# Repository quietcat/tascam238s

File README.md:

# The Missing Tascam 238S Service Manual
Tascam 238S schematics and additional information. The Dolby S daughtercards are also used in Tascam MSR

## rp-amp-pcb

https://github.com/quietcat/tascam238s/blob/main/rp-amp-pcb.pdf

Contains Kicad schematics for the part of Tascam 238S channel PCB that is different from the dbx version

## dolby-hic

https://github.com/quietcat/tascam238s/blob/main/dolby-hic.pdf

Contains Kicad schematics for Dolby S NR HIC PCB, a Dolby encoder/decoder daughtercard for Tascam 238S

https://github.com/quietcat/tascam238s/tree/main/dolby-hic/gerbers contains Gerber files for a replacement Dolby PCB. The layout is different from the original, but functionally it is the same.

Visit https://238pro.com for more information on Tascam 238/238S repair and service

## 238S Calibration

First, calibrate the unit with Dolby S out.

Set all channels to recording mode, then press Pause and Record.

Feed -10 dBV/0 dBVU 400Hz (316 mV RMS) signal to the line inputs, and use ENC ADJ trimmer to adjust AC voltage on TP1 to be 388 mV.

Use ENC OUT trimmer to adjust AC voltage on REC LEVEL trimmer input lead (closest to the front) to be the same in both Dolby IN and OUT modes on each channel.

With Dolby S OUT, make a recording of -10 dBV/0 dBVU 400Hz test tone on all channels.

Set Dolby to IN, play back the recording and use DEC ADJ trimmer to adjust AC voltage on TP1 to be 388 mV on all channels.

Use DEC OUT trimmer to set voltage on the line out to -10 dBV (316 mV) on all channels.

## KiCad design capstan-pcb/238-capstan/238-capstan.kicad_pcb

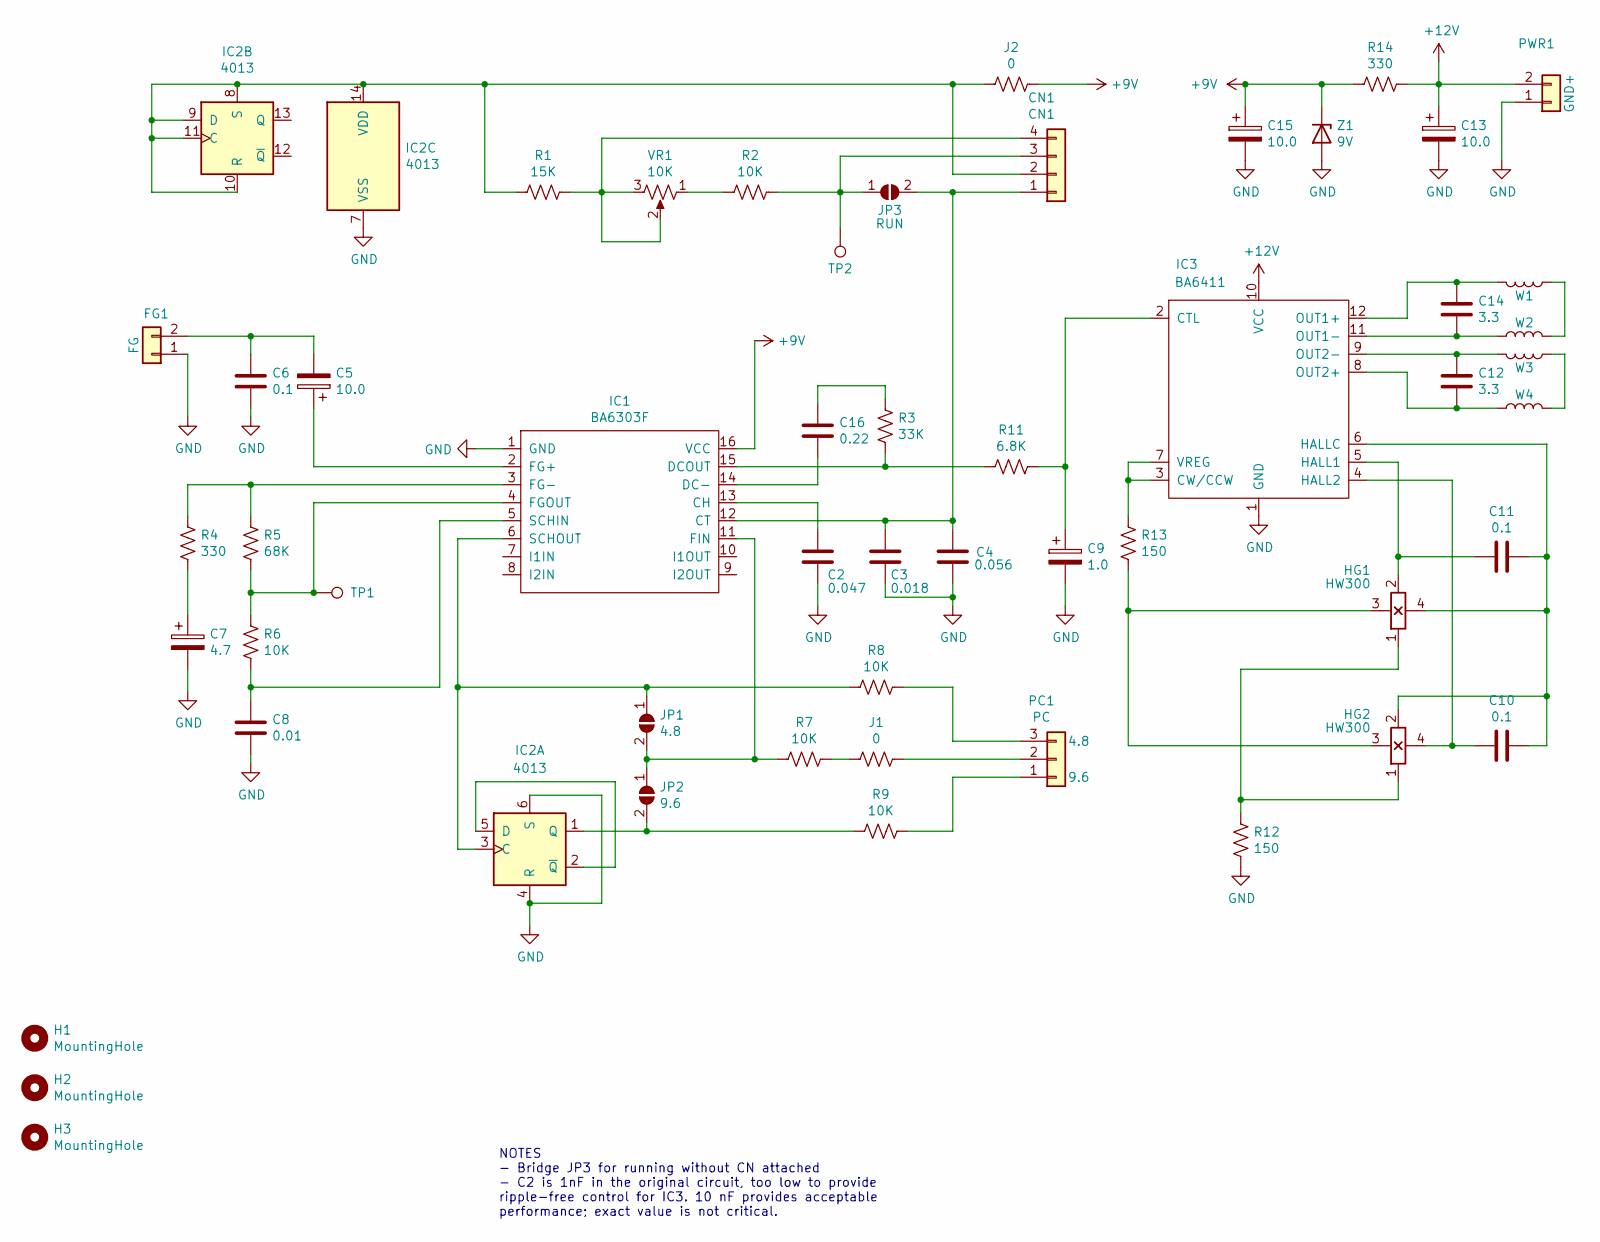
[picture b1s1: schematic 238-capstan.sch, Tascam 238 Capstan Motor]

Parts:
C2: 0.047; C_1206_3216Metric_Pad1.33x1.80mm_HandSolder
C3: 0.018; 238_C3
C4: 0.056; 238_C4
C5, C13, C15: 10.0; CP_Elec_4x5.3
C6, C10, C11: 0.1; C_1206_3216Metric_Pad1.33x1.80mm_HandSolder
C7: 4.7; CP_Elec_4x5.3
C8: 0.01; C_1206_3216Metric_Pad1.33x1.80mm_HandSolder
C9: 1.0; CP_Elec_4x5.3
C12, C14: 3.3; CP_Elec_4x5.3
C16: 0.22; C_1206_3216Metric_Pad1.33x1.80mm_HandSolder
CN1: CN1; 238_4_wire_conn
FG1: FG; 238_2_wire_conn
H1, H2, H3: MountingHole; MountingHole_2.1mm
HG1, HG2: HW300
IC1: BA6303F; SOIC-16_4.55x10.3mm_P1.27mm
IC2: 4013; SO-14_5.3x10.2mm_P1.27mm
IC3: BA6411
J1, J2: 0; R_1206_3216Metric_Pad1.30x1.75mm_HandSolder
JP1: 4.8; SolderJumper-2_P1.3mm_Open_RoundedPad1.0x1.5mm
JP2: 9.6; SolderJumper-2_P1.3mm_Open_RoundedPad1.0x1.5mm
JP3: RUN; SolderJumper-2_P1.3mm_Open_RoundedPad1.0x1.5mm
PC1: PC; 238_3_wire_conn
PWR1: GND+; 238_2_wire_conn
R1: 15K; R_1206_3216Metric_Pad1.30x1.75mm_HandSolder
R2, R6, R7, R8, R9: 10K; R_1206_3216Metric_Pad1.30x1.75mm_HandSolder
R3: 33K; R_1206_3216Metric_Pad1.30x1.75mm_HandSolder
R4, R14: 330; R_1206_3216Metric_Pad1.30x1.75mm_HandSolder
R5: 68K; R_1206_3216Metric_Pad1.30x1.75mm_HandSolder
R11: 6.8K; R_1206_3216Metric_Pad1.30x1.75mm_HandSolder
R12, R13: 150; R_1206_3216Metric_Pad1.30x1.75mm_HandSolder
TP1: TP1; TestPoint_Pad_D1.5mm
TP2: TP2; TestPoint_Pad_D2.5mm
VR1: 10K; Potentiometer_Bourns_TC33X_Vertical
W1, W2, W3, W4: W; 238_winding
Z1: 9V; D_MiniMELF

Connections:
+9V: C15.1, IC1.16 (VCC), J2.1, R14.2, Z1.1 (K)
+12V: C13.1, IC3.10 (VCC), PWR1.2, R14.1
GND: C2.2, C3.1, C4.2, C6.2, C7.2, C8.2, C9.2, C13.2, C15.2, FG1.1, IC1.1 (GND), IC2.4 (R), IC2.6 (S), IC2.7 (VSS), IC3.1 (GND), PWR1.1, R12.2, Z1.2 (A)
unnamed: C2.1, IC1.13 (CH)
unnamed: C3.2, C4.1, CN1.1, IC1.12 (CT), JP3.2 (B)
unnamed: C5.1, IC1.2 (FG+)
unnamed: C5.2, C6.1, FG1.2
unnamed: C7.1, R4.2
unnamed: C8.1, IC1.5 (SCHIN), R6.2
unnamed: C9.1, IC3.2 (CTL), R11.1
unnamed: C10.1, HG2.4 (UH2), IC3.4 (HALL2)
unnamed: C10.2, C11.2, HG1.4 (UH2), HG2.2 (U2), IC3.6 (HALLC)
unnamed: C11.1, HG1.2 (U2), IC3.5 (HALL1)
unnamed: C12.1, IC3.8 (OUT2+), W4.1
unnamed: C12.2, IC3.9 (OUT2-), W3.2
unnamed: C14.1, IC3.11 (OUT1-), W2.1
unnamed: C14.2, IC3.12 (OUT1+), W1.2
unnamed: C16.1, R3.1
unnamed: C16.2, IC1.14 (DC-)
unnamed: CN1.2, IC2.8 (S), IC2.9 (D), IC2.10 (R), IC2.11 (C), IC2.14 (VDD), J2.2, R1.2
unnamed: CN1.3, JP3.1 (A), R2.1, TP2.1
unnamed: CN1.4, R1.1, VR1.2, VR1.3
unnamed: HG1.1 (U1), HG2.1 (U1), R12.1
unnamed: HG1.3 (UH1), HG2.3 (UH1), R13.2
unnamed: IC1.3 (FG-), R4.1, R5.1
unnamed: IC1.4 (FGOUT), R5.2, R6.1, TP1.1
unnamed: IC1.6 (SCHOUT), IC2.3 (C), JP1.1 (A), R8.2
unnamed: IC1.11 (FIN), JP1.2 (B), JP2.1 (A), R7.2
unnamed: IC1.15 (DCOUT), R3.2, R11.2
unnamed: IC2.1 (Q), JP2.2 (B), R9.2
unnamed: IC2.2 (~Q), IC2.5 (D)
unnamed: IC3.3 (CW/CCW), IC3.7 (VREG), R13.1
unnamed: J1.1, PC1.2
unnamed: J1.2, R7.1
unnamed: PC1.1, R9.1
unnamed: PC1.3, R8.1
unnamed: R2.2, VR1.1
unnamed: W1.1, W2.2
unnamed: W3.1, W4.2

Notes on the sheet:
NOTES - Bridge JP3 for running without CN attached - C2 is 1nF in the original circuit, too low to provide ripple-free control for IC3. 10 nF provides acceptable performance; exact value is not critical.

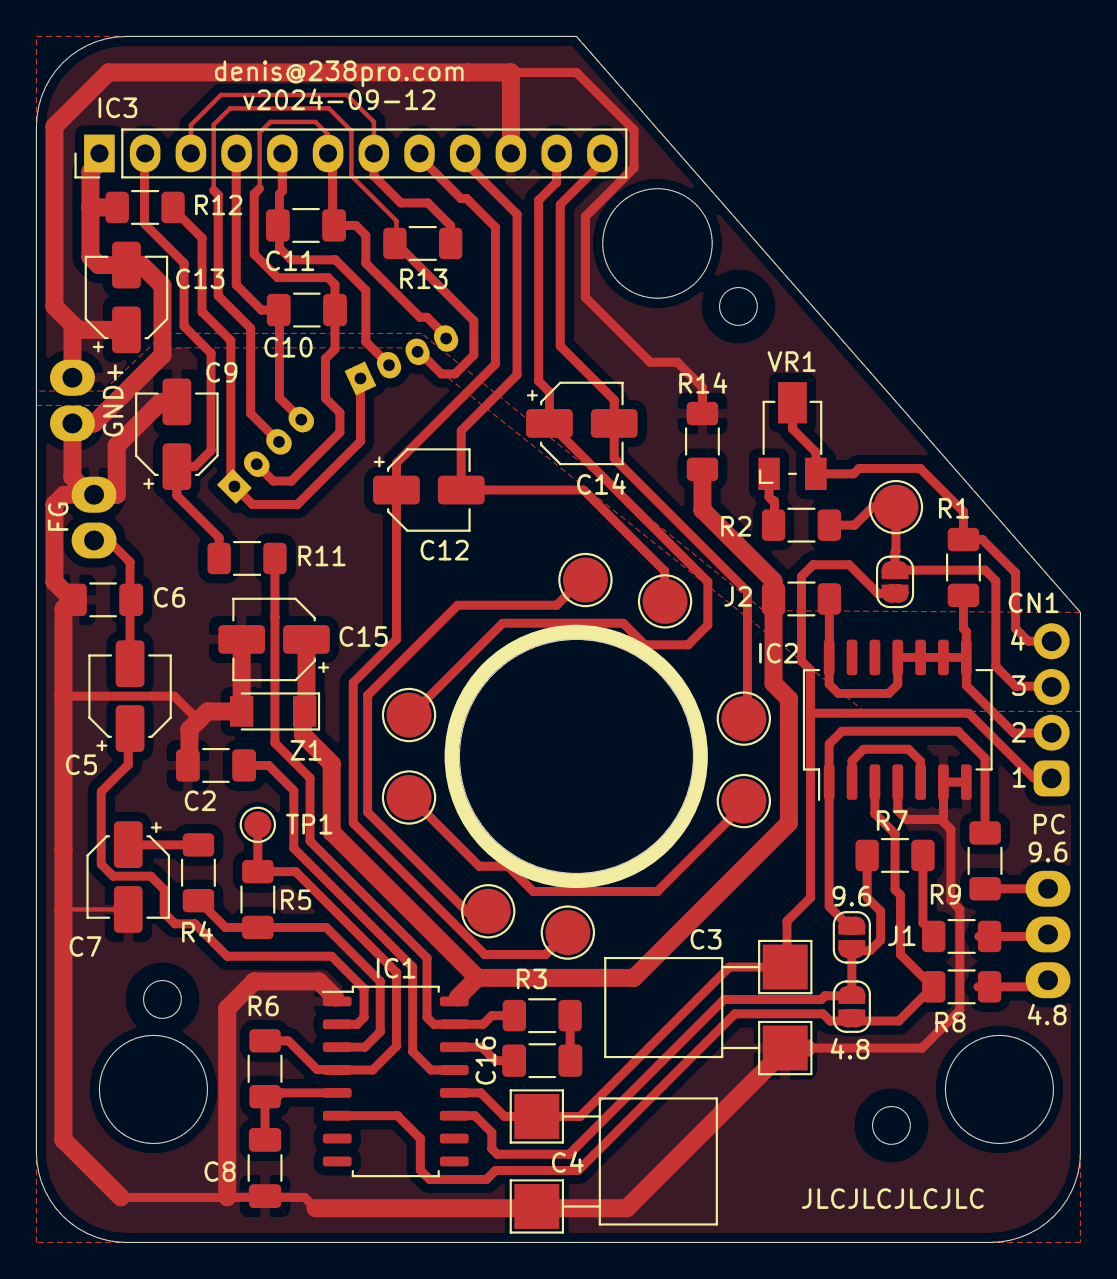
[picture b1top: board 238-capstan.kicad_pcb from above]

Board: 2 copper layers, 58.0 x 67.0 mm, 53 parts (0 on the bottom side), 39 nets.

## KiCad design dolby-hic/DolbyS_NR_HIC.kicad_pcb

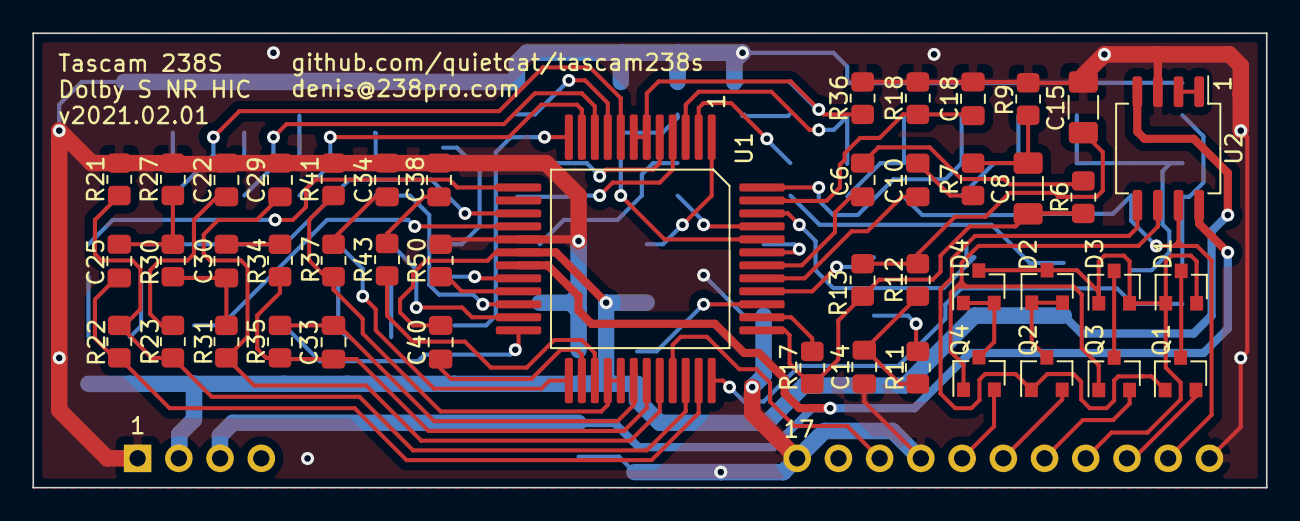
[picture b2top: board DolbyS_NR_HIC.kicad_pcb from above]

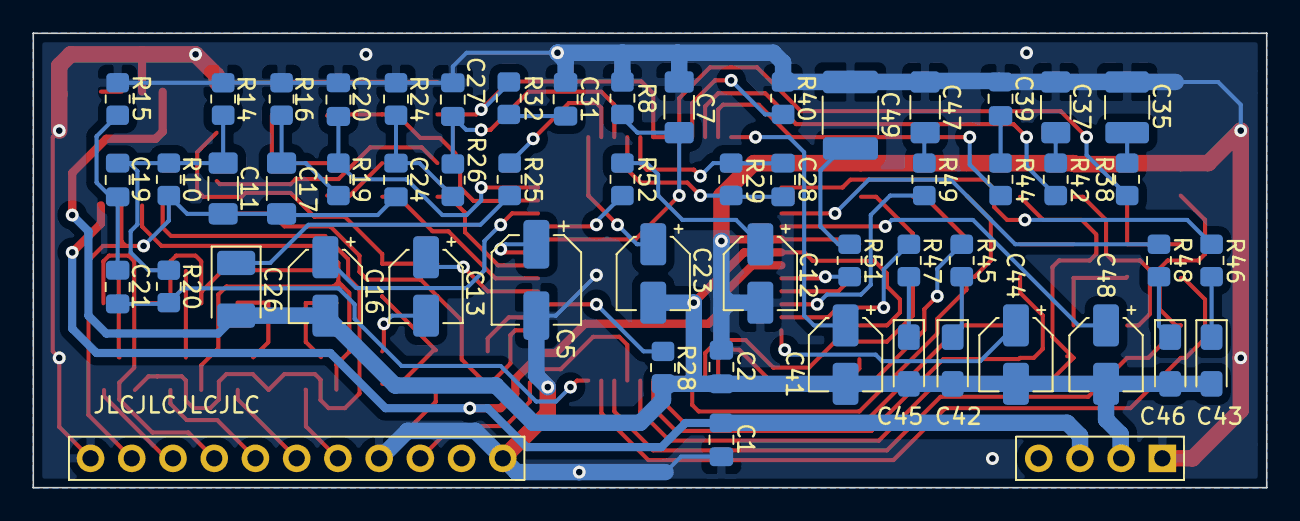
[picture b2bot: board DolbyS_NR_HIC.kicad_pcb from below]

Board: 2 copper layers, 76.0 x 28.0 mm, 100 parts (55 on the bottom side), 86 nets.

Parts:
C1, C2: 470n; C_0805_2012Metric_Pad1.18x1.45mm_HandSolder
C5: 22u; CP_Elec_5x5.8
C6, C19, C21, C22: 1.8n; C_0805_2012Metric_Pad1.18x1.45mm_HandSolder
C7, C8, C11, C15, C17: 100n; C_1206_3216Metric_Pad1.33x1.80mm_HandSolder
C10: 18n; C_0805_2012Metric_Pad1.18x1.45mm_HandSolder
C12: 10u; CP_Elec_4x5.8
C13: 0.47u; CP_Elec_4x5.8
C14, C20: 22n; C_0805_2012Metric_Pad1.18x1.45mm_HandSolder
C16, C23: 0.22u; CP_Elec_4x5.8
C18: 18(33)n; C_0805_2012Metric_Pad1.18x1.45mm_HandSolder
C24, C25: 39n; C_0805_2012Metric_Pad1.18x1.45mm_HandSolder
C26: 1.0u; CP_EIA-3528-21_Kemet-B_Pad1.50x2.35mm_HandSolder
C27: 680p; C_0805_2012Metric_Pad1.18x1.45mm_HandSolder
C28, C33: 1n; C_0805_2012Metric_Pad1.18x1.45mm_HandSolder
C29: 470p; C_0805_2012Metric_Pad1.18x1.45mm_HandSolder
C30: 2.2n; C_0805_2012Metric_Pad1.18x1.45mm_HandSolder
C31, C34: 8.2n; C_0805_2012Metric_Pad1.18x1.45mm_HandSolder
C35: 220n; C_1210_3225Metric_Pad1.33x2.70mm_HandSolder
C37, C47: 82n; C_1206_3216Metric_Pad1.33x1.80mm_HandSolder
C38, C39: 15n; C_0805_2012Metric_Pad1.18x1.45mm_HandSolder
C40: 47n; C_0805_2012Metric_Pad1.18x1.45mm_HandSolder
C41, C44, C48: 0.1u; CP_Elec_4x5.8
C42, C46: 0.22u; CP_EIA-3216-18_Kemet-A_Pad1.58x1.35mm_HandSolder
C43, C45: 0.47u; CP_EIA-3216-18_Kemet-A_Pad1.58x1.35mm_HandSolder
C49: 330n; C_1812_4532Metric
D1, D2, D3, D4: MMBD914; SOT-23
J1: DOLBY_S_CONN
Q1, Q3: MMBFJ270; SOT-23
Q2, Q4: MMBFJ201; SOT-23
R6, R11, R12: 30k; R_0805_2012Metric_Pad1.20x1.40mm_HandSolder
R7: 36k; R_0805_2012Metric_Pad1.20x1.40mm_HandSolder
R8, R14: 16k; R_0805_2012Metric_Pad1.20x1.40mm_HandSolder
R9, R20, R23, R36, R41: 5.1k; R_0805_2012Metric_Pad1.20x1.40mm_HandSolder
R10: 27k; R_0805_2012Metric_Pad1.20x1.40mm_HandSolder
R13, R22: 11k; R_0805_2012Metric_Pad1.20x1.40mm_HandSolder
R15, R42, R49: 2.4k; R_0805_2012Metric_Pad1.20x1.40mm_HandSolder
R16, R19: 39k; R_0805_2012Metric_Pad1.20x1.40mm_HandSolder
R17: 20k; R_0805_2012Metric_Pad1.20x1.40mm_HandSolder
R18: 22(11)k; R_0805_2012Metric_Pad1.20x1.40mm_HandSolder
R21: 91(68)k; R_0805_2012Metric_Pad1.20x1.40mm_HandSolder
R24, R27: 10k; R_0805_2012Metric_Pad1.20x1.40mm_HandSolder
R25, R46, R47: 33; R_0805_2012Metric_Pad1.20x1.40mm_HandSolder
R26: 18k; R_0805_2012Metric_Pad1.20x1.40mm_HandSolder
R28: 24k; R_0805_2012Metric_Pad1.20x1.40mm_HandSolder
R29, R35: 820k; R_0805_2012Metric_Pad1.20x1.40mm_HandSolder
R30, R52: 8.2k; R_0805_2012Metric_Pad1.20x1.40mm_HandSolder
R31: 13k; R_0805_2012Metric_Pad1.20x1.40mm_HandSolder
R32, R37: 1.6k; R_0805_2012Metric_Pad1.20x1.40mm_HandSolder
R34: 1.5k; R_0805_2012Metric_Pad1.20x1.40mm_HandSolder
R38, R43: 1.8k; R_0805_2012Metric_Pad1.20x1.40mm_HandSolder
R40, R50: 4.7k; R_0805_2012Metric_Pad1.20x1.40mm_HandSolder
R44: 1.3k; R_0805_2012Metric_Pad1.20x1.40mm_HandSolder
R45, R48: 47; R_0805_2012Metric_Pad1.20x1.40mm_HandSolder
R51: 1.2k; R_0805_2012Metric_Pad1.20x1.40mm_HandSolder
U1: CXA1417Q; QFP-48_12x12mm_P0.8mm
U2: NE5532A; SO-8_5.3x6.2mm_P1.27mm

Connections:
/DEC_FB: J1.23, Q3.2
/DEC_IN: J1.25, Q1.2
/DEC_OUT: C11.1, C17.1, C24.2, J1.26, R10.1, U2.7
/Dolby S Encoder/N1: R32.2, R36.2, U1.6, U1.7
/Dolby S Encoder/N2: R37.1, R41.1, U1.28, U1.29
/ENC_FB: J1.21, Q4.2
/ENC_IN: J1.22, Q2.2
/ENC_OUT: J1.19, U1.33
/SEL: D1.1, D1.2, D2.3, D3.1, D3.2, D4.3, J1.24
GND: C1.2, C2.2, C5.2, C7.2, C12.2, C14.2, C15.2, C18.2, C20.2, C22.2, C27.2, C29.2, C31.1, C34.2, C35.1, C37.1, C38.2, C39.1, C47.1, C49.1, J1.1, J1.17, J1.20, J1.27, R8.2, R9.1, R14.1, R15.1, R16.1, R18.2, R21.2, R24.2, R27.1, R36.1, R40.1, R41.2, R50.1, U1.17, U2.3
unnamed: C5.1, U1.43
unnamed: C6.1, U1.42
unnamed: C6.2, R6.1
unnamed: C7.1, R8.1, U1.44
unnamed: C8.1, R7.2, R9.2
unnamed: C8.2, R6.2, R13.2, R17.2, U1.37
unnamed: C10.1, U1.41
unnamed: C10.2, R7.1
unnamed: C11.2, C19.1, R10.2, R14.2, R20.1
unnamed: C12.1, R52.2
unnamed: C13.1, U1.40
unnamed: C13.2, R11.1
unnamed: C14.1, R11.2, R12.2
unnamed: C15.1, R12.1, R13.1
unnamed: C16.1, U1.46
unnamed: C17.2, R16.2, R19.1
unnamed: C18.1, R18.1, U1.47
unnamed: C19.2, C21.2, R15.2
unnamed: C20.1, R19.2, U1.48
unnamed: C21.1, R20.2, U1.36
unnamed: C22.1, R23.2
unnamed: C23.1, U1.1
unnamed: C24.1, R24.1, R26.1
unnamed: C25.1, R22.2, U1.35
unnamed: C25.2, R27.2, R30.2
unnamed: C26.1, R25.2
unnamed: C27.1, R26.2, U1.3
unnamed: C28.1, R29.1, U1.4
unnamed: C28.2, R29.2, U1.5
unnamed: C29.1, R31.1, U1.32
unnamed: C30.1, R34.2
unnamed: C30.2, R30.1, R31.2
unnamed: C31.2, R32.1
unnamed: C33.1, R35.1, U1.30
unnamed: C33.2, R34.1, R35.2, U1.31
unnamed: C34.1, R37.2
unnamed: C35.2, R38.1
unnamed: C37.2, R42.1
unnamed: C38.1, R43.2
unnamed: C39.2, R44.1
unnamed: C40.1, U1.26
unnamed: C41.1, U1.12
unnamed: C42.1, R45.2
unnamed: C43.1, R46.1
unnamed: C44.1, U1.24
unnamed: C45.1, R47.1
unnamed: C46.1, R48.1
unnamed: C47.2, R49.1
unnamed: C48.1, U1.16
unnamed: C49.2, R51.1
unnamed: D1.3, Q1.3
unnamed: D2.1, D2.2, Q2.3
unnamed: D3.3, Q3.3
unnamed: D4.1, D4.2, Q4.3
unnamed: Q1.1, Q2.1, U2.5
unnamed: Q3.1, Q4.1, U2.6
unnamed: R17.1, U1.38
unnamed: R21.1, R22.1, R23.1, U1.34
unnamed: R25.1, U1.2
unnamed: R28.1, U1.39
unnamed: R38.2, U1.8
unnamed: R40.2, U1.9
unnamed: R42.2, U1.10
unnamed: R43.1, U1.27
unnamed: R44.2, U1.11
unnamed: R45.1, U1.25
unnamed: R46.2, U1.13
unnamed: R47.2, U1.23
unnamed: R48.2, U1.15
unnamed: R49.2, U1.22
unnamed: R50.2, U1.21
unnamed: R51.2, U1.20
unnamed: R52.1, U1.45
unnamed: U2.1, U2.2
VCC: C1.1, J1.3, U1.19, U2.8
VEE: C2.1, C16.2, C23.2, C26.2, C40.2, C41.2, C42.2, C43.2, C44.2, C45.2, C46.2, C48.2, J1.2, R28.2, U1.18, U2.4

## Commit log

2020-10-24 Add values
2020-10-24 Remove backup file from repo
2020-10-25 Removed cache lib
2020-10-25 Latest schematics
2020-10-25 Updated version on Dolby hic
2020-10-26 Fixed version on hic main page
2020-10-28 Fix swapped pins on transistors on hic; add clarification about GND and VCT buses on hic
2020-10-28 Add pdf versions of the schematics; remove blank page layout description file
2020-10-28 Add project library reference file
2020-11-01 Version 2020.10.30 of schematic - fixed error in input circuit on HIC; HIC pcb version 2020.10.31 with gerbers sent to fab
2020-11-01 Updated pdf for hic
2020-11-02 Minor clarification updates to the hic
2020-11-04 Minor PCB rouing change, eliminated two vias
2020-11-14 Update README.md
    Added calibration procedure from the website
2021-01-12 dolby-hic PCB version 2021.01.10 - moved all electrolytical caps to the back of the board; both chips and input switching transistors on the front
2021-03-05 Update README to reflect new knowledge on calibration process
2021-03-11 Updated HIC layout; RP amp clarification
2024-08-04 Added capstan PCB design v2024-08-03
2024-08-06 Capstan pcb v2024-08-04
2024-08-06 Capstan PCB v2024-08-06
2024-08-06 Capstan PCB v2024-08-06 pour +12V
2024-08-07 Capstan PCB - fix copper pour DRC errors, fix ground routing and keepout areas around FG input
2024-08-14 Capstan PCB fix mouting hole position; larger pads for VR1; routing adjustments
2024-08-16 Capstan PCB gerbers v2024-08-15, minor tweaks, sent to fab
2024-08-28 Add capstan pcb PDF
2024-09-13 Capstan PCB v2024-09-11, clarified schematic
2024-09-13 Capstan PCB gerbers v2024-09-12
